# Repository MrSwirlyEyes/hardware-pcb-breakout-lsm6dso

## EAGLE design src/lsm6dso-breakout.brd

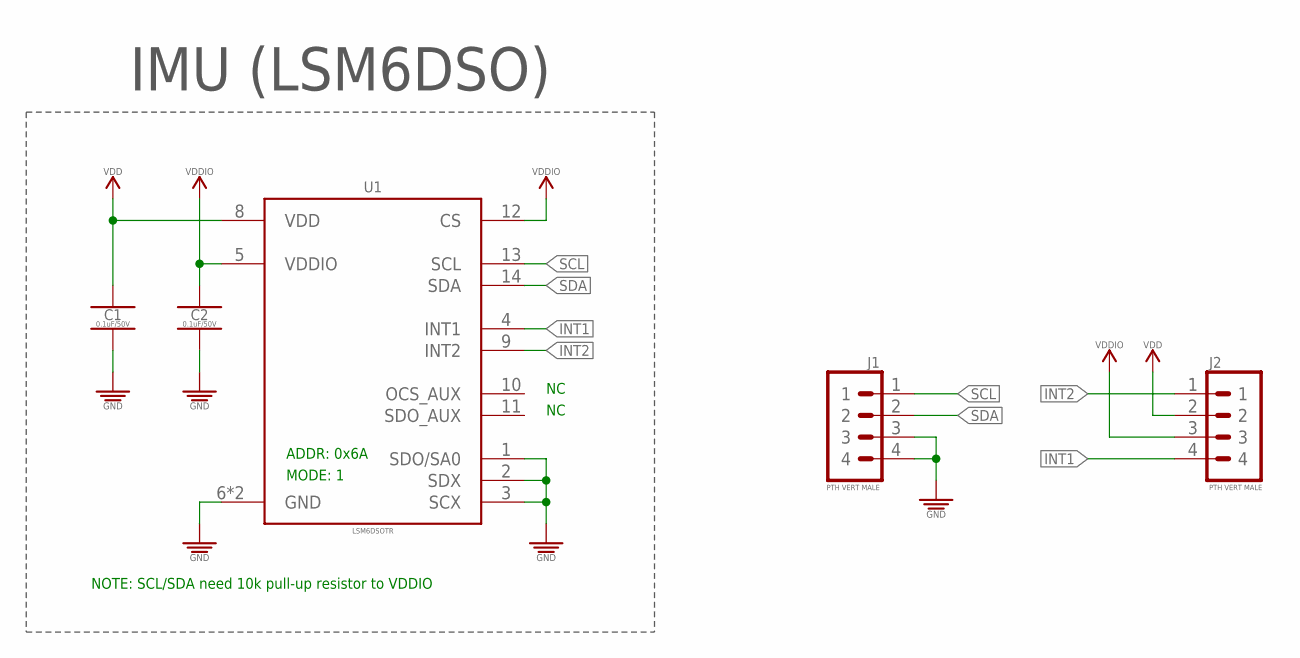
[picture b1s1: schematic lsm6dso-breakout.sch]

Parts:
C1, C2: 0.1uF/50V; CAPC1005X55_SMD-0402
J1, J2: PTH VERT MALE; HDRV4W64P254_1X4_1016X254X838B
U1: LSM6DSOTR; QFN50P250X300X86-14N

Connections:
GND: C1.2, C2.2, J1.3, J1.4, U1.1 (SDO/SA0), U1.2 (SDX), U1.3 (SCX), U1.6 (GND), U1.7 (GND)
INT1: J2.4, U1.4 (INT1)
INT2: J2.1, U1.9 (INT2)
SCL: J1.1, U1.13 (SCL)
SDA: J1.2, U1.14 (SDA)
VDD: C1.1, J2.2, U1.8 (VDD)
VDDIO: C2.1, J2.3, U1.5 (VDDIO), U1.12 (CS)

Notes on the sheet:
MODE: 1
ADDR: 0x6A
NOTE: SCL/SDA need 10k pull-up resistor to VDDIO
IMU (LSM6DSO)

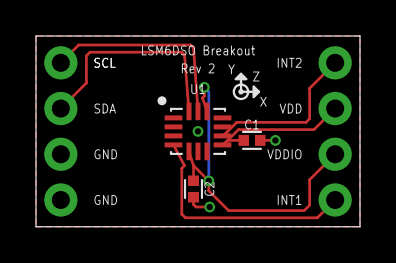
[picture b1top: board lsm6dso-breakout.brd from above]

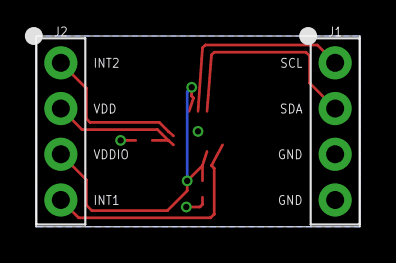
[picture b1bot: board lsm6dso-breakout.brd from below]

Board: 2 copper layers, 18.0 x 10.6 mm, 5 parts (2 on the bottom side), 7 nets.

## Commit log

2021-01-12 [Rev 1] - Initialize repo.
2021-08-11 Update CAM files.
